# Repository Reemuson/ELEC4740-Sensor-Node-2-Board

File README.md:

<h1 align="center">SN2 BREAKOUT BOARD</h1>

<p align="center" width="100%">
  
</p>

***

<p align="center">
  
&nbsp; &nbsp; &nbsp; &nbsp;
  
</p>

***

## SPECIFICATIONS

| Parameter | Value | 
| --- | --- |
| Dimensions | 100.0 × 100.0 mm |

***

## DIRECTORY STRUCTURE

    .
    ├─ Computations       # Misc calculations
    ├─ HTML               # HTML files for generated webpage
    ├─ Images             # Pictures and renders
    │
    ├─ kibot_resources    # External resources for KiBot
    │  ├─ colors          # Color theme for KiCad
    │  ├─ fonts           # Fonts used in the project
    │  ├─ scripts         # External scripts used with KiBot
    │  └─ templates       # Templates for KiBot generated reports
    │
    ├─ kibot_yaml         # KiBot YAML config files
    ├─ KiRI               # KiRI (PCB diff viewer) files
    │
    ├─ lib                # KiCad footprint and symbol libraries
    │  ├─ 3d_models       # Component 3D models
    │  ├─ lib_fp          # Footprint libraries
    │  └─ lib_sym         # Symbol libraries
    │
    ├─ Logos              # Logos
    │
    ├─ Manufacturing      # Assembly and fabrication documents
    │  ├─ Assembly        # Assembly documents (BoM, pos, notes)
    │  │
    │  └─ Fabrication     # Fabrication documents (ZIP, notes)
    │     ├─ Drill Tables # CSV drill tables
    │     └─ Gerbers      # Gerbers
    │
    ├─ Report             # Reports for ERC/DRC
    ├─ Schematic          # PDF of schematic
    ├─ Templates          # Title block templates
    ├─ Testing
    │  └─ Testpoints      # Testpoints tables      
    │
    └─ Variants           # Outputs for assembly variants

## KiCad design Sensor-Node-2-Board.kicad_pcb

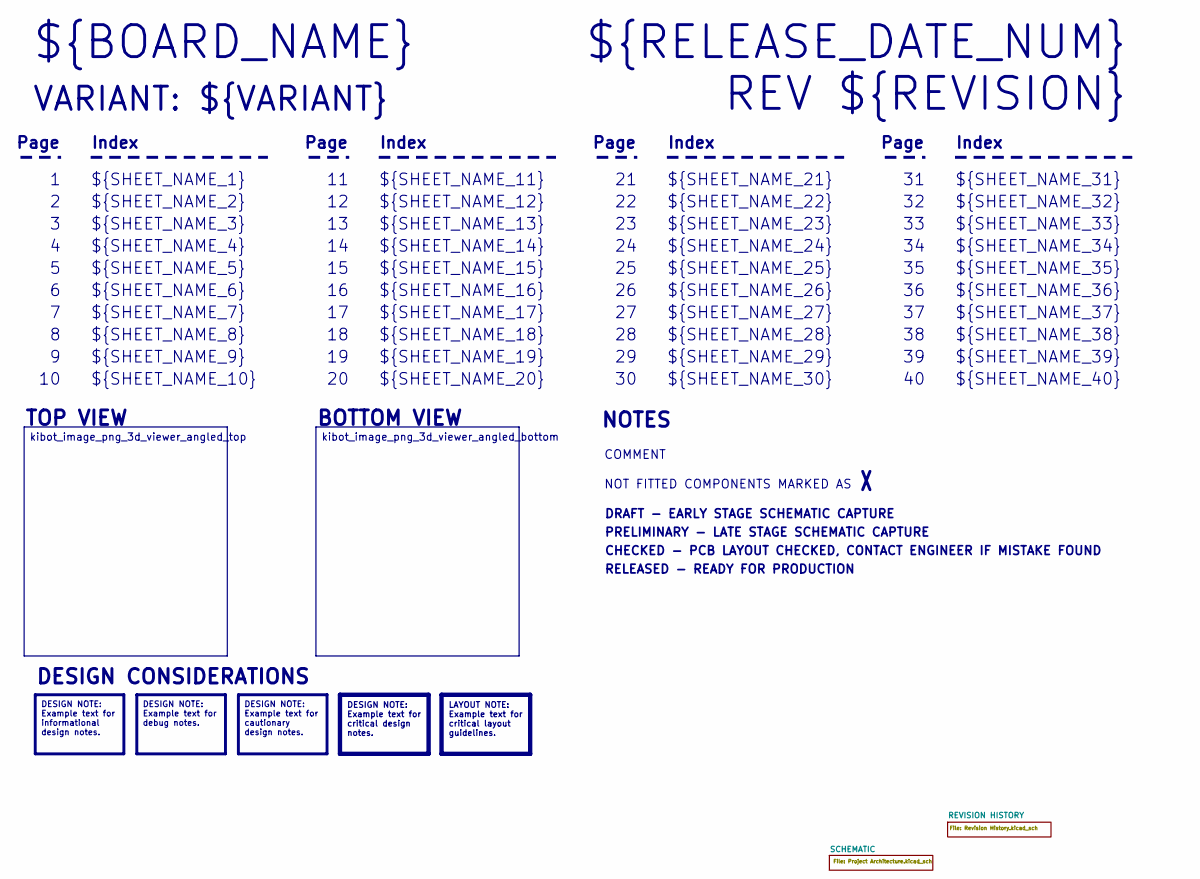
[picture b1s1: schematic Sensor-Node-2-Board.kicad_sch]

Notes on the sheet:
VARIANT: ${VARIANT}
RELEASED - READY FOR PRODUCTION
${SHEET_NAME_24}
Index
Page
PRELIMINARY - LATE STAGE SCHEMATIC CAPTURE
${SHEET_NAME_22}
DRAFT - EARLY STAGE SCHEMATIC CAPTURE
${SHEET_NAME_12}
${SHEET_NAME_8}
${SHEET_NAME_2}
${SHEET_NAME_5}
${SHEET_NAME_20}
${SHEET_NAME_23}
${RELEASE_DATE_NUM}
${SHEET_NAME_35}
NOT FITTED COMPONENTS MARKED AS
${SHEET_NAME_11}
${SHEET_NAME_6}
${SHEET_NAME_37}
${SHEET_NAME_26}
${SHEET_NAME_36}
REV ${REVISION}
${SHEET_NAME_15}
CHECKED - PCB LAYOUT CHECKED, CONTACT ENGINEER IF MISTAKE FOUND
BOTTOM VIEW
${SHEET_NAME_14}
${SHEET_NAME_21}
${SHEET_NAME_17}
${SHEET_NAME_18}
${SHEET_NAME_7}
${SHEET_NAME_31}
${BOARD_NAME}
NOTES
${SHEET_NAME_40}
${SHEET_NAME_39}
${SHEET_NAME_32}
${SHEET_NAME_1}
${SHEET_NAME_9}
${SHEET_NAME_38}

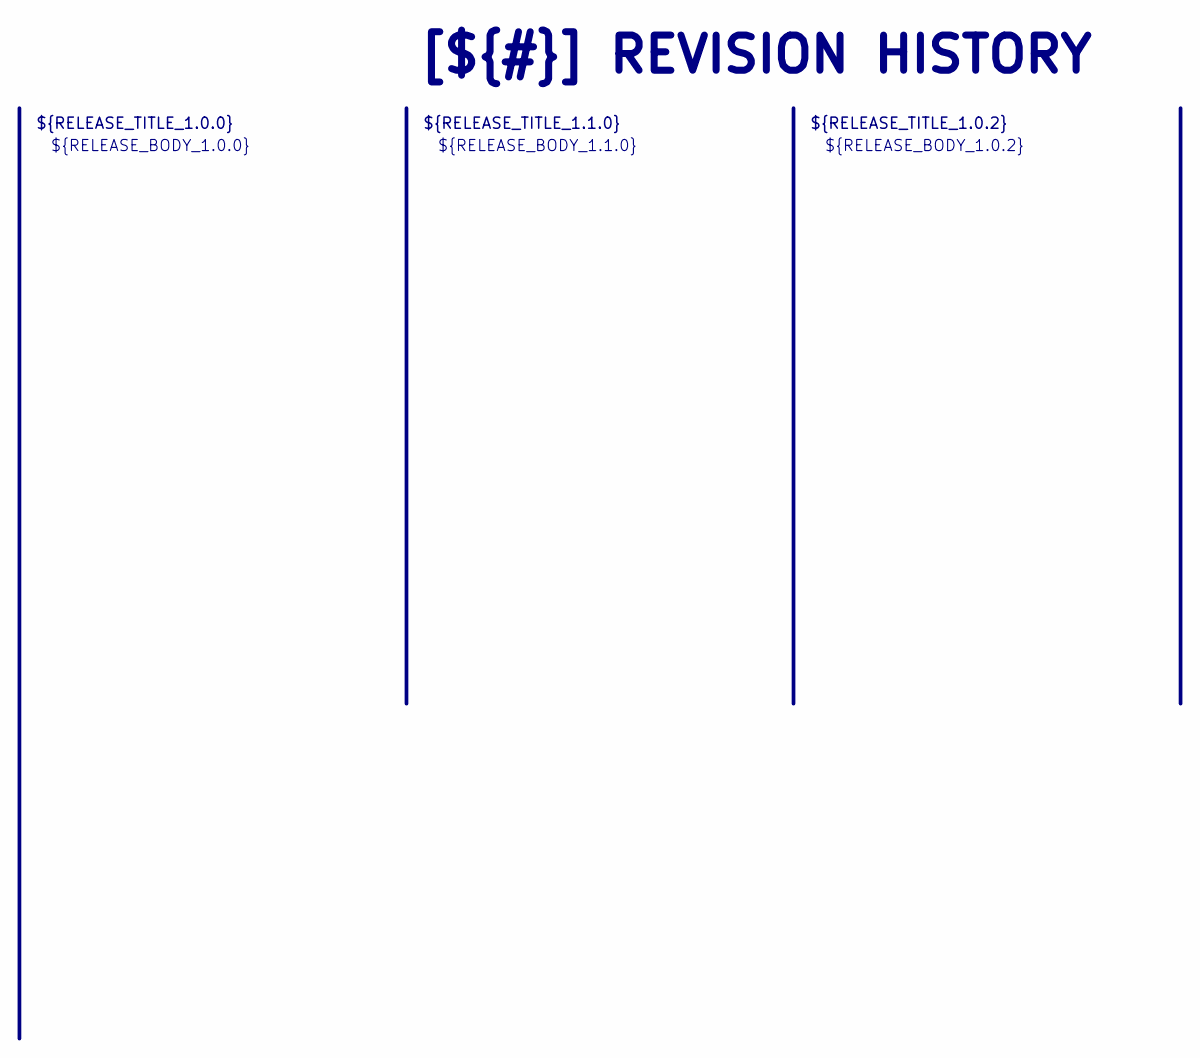
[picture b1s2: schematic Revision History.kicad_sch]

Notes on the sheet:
[${#}] ${TITLE}
${RELEASE_BODY_1.0.0}
${RELEASE_TITLE_1.0.2}
${RELEASE_BODY_1.0.2}
${RELEASE_BODY_1.1.0}
${RELEASE_TITLE_1.0.0}
${RELEASE_TITLE_1.1.0}

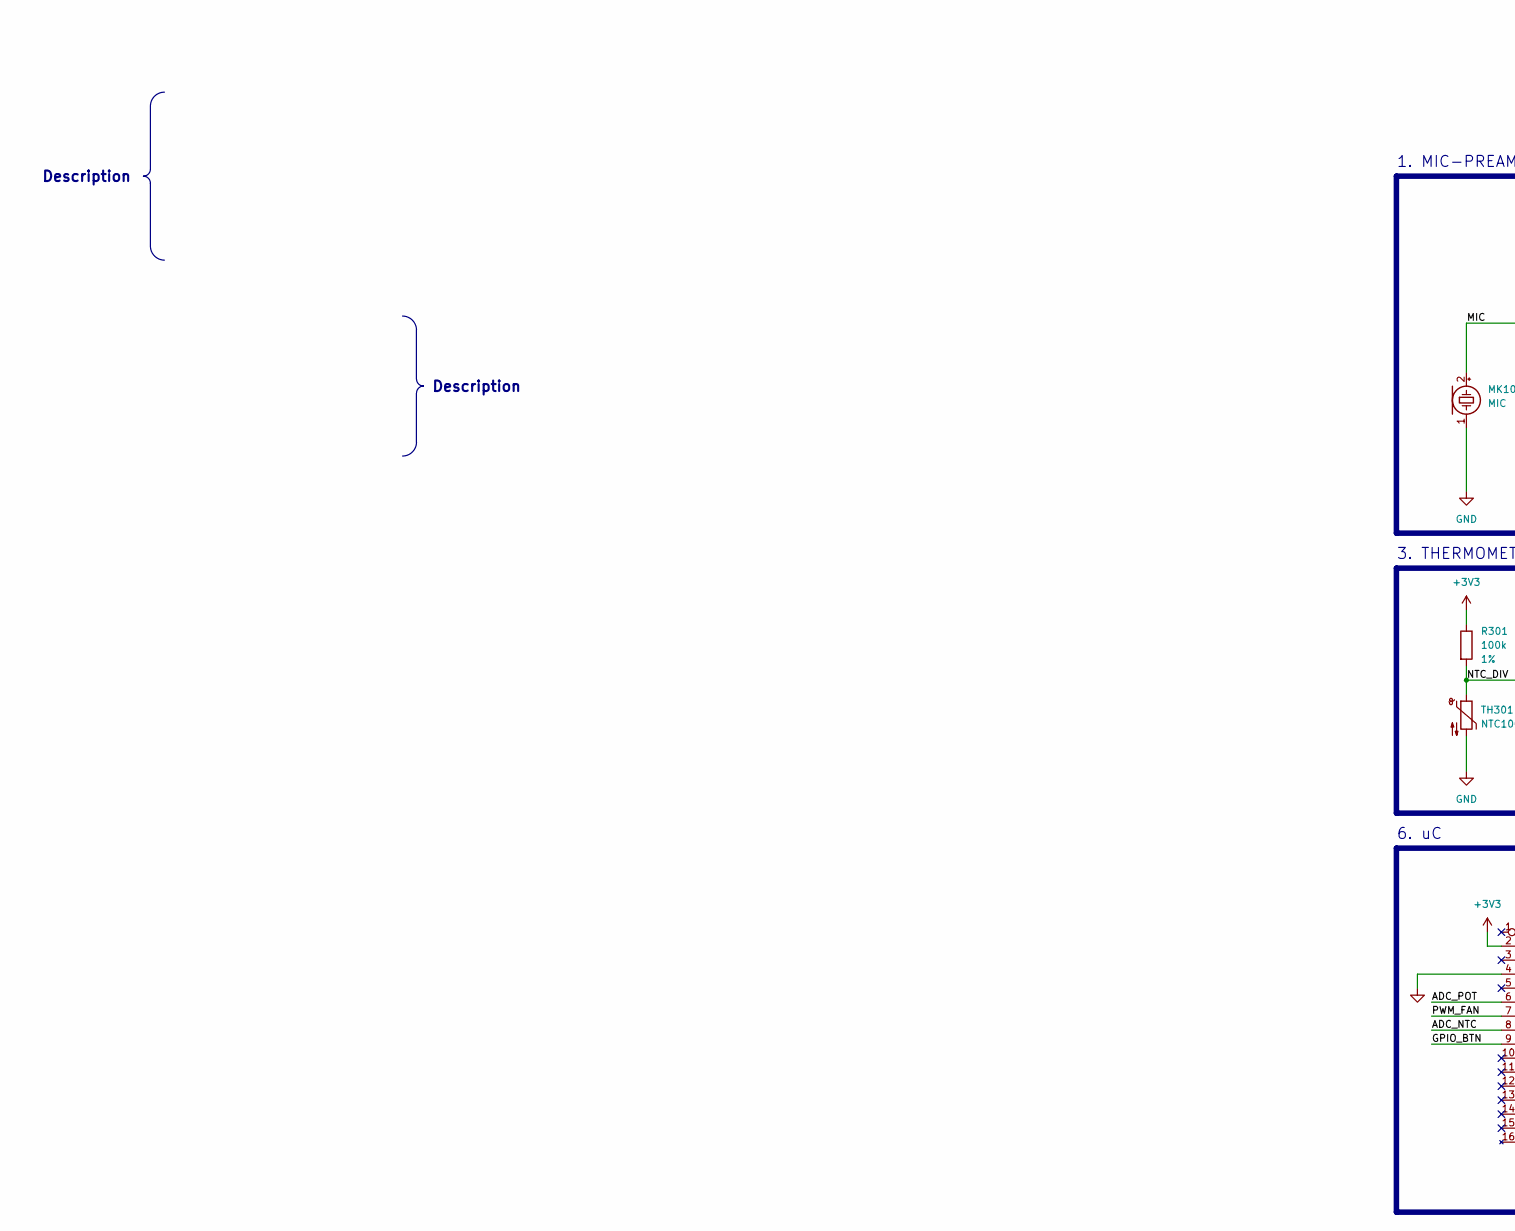
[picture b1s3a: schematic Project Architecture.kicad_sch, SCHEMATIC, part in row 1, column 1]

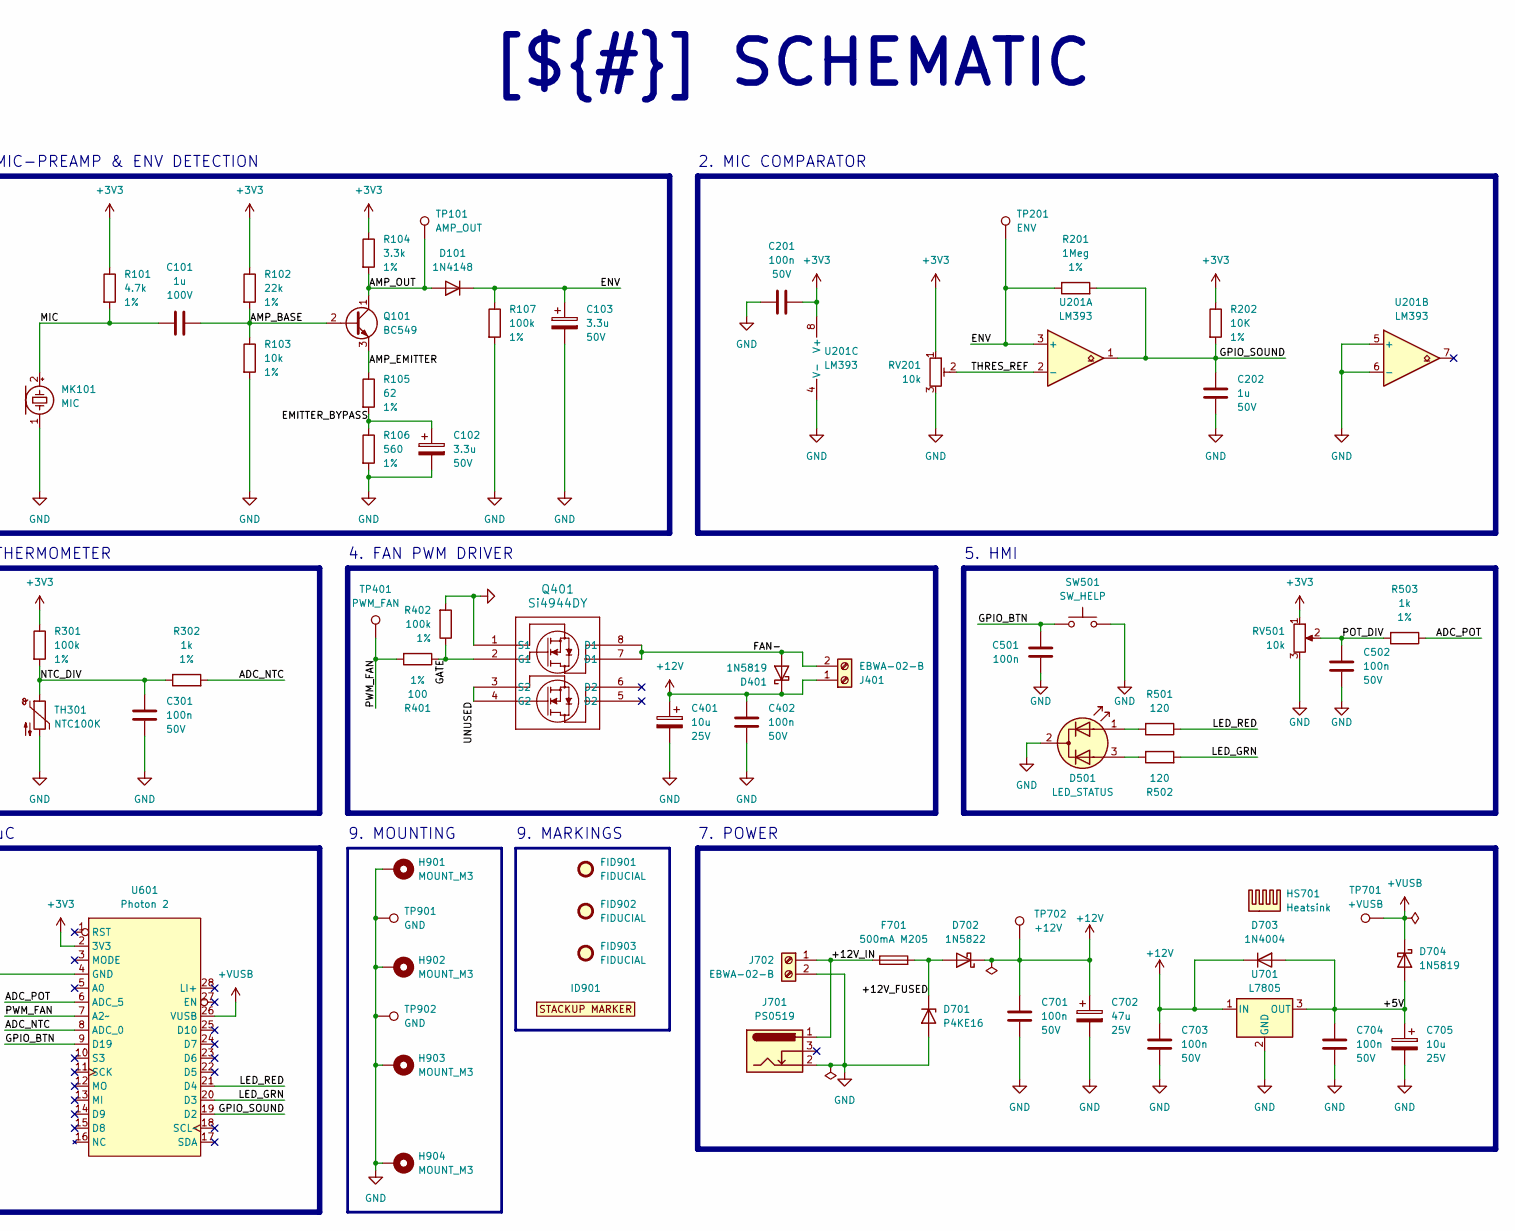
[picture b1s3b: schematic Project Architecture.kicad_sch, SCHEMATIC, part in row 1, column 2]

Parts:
C101: 1u; C_Rect_L16.5mm_W6.0mm_P15.00mm_MKT; Voltage 100V
C102, C103: 3.3u; CP_Radial_D5.0mm_P2.00mm; Voltage 50V; Tolerance 10%
C201, C301, C402, C501, C502, C701, C703, C704: 100n; C_Disc_D5.0mm_W2.5mm_P5.00mm; Tolerance 20%; Voltage 50V
C202: 1u; C_Disc_D5.0mm_W2.5mm_P5.00mm; Voltage 50V
C401, C705: 10u; CP_Radial_D5.0mm_P2.00mm; Voltage 25V
C702: 47u; CP_Radial_D8.0mm_P3.50mm; Voltage 25V
D101: 1N4148; D_DO-35_SOD27_P5.08mm_Vertical_AnodeUp
D401: 1N5819; D_DO-41_SOD81_P7.62mm_Horizontal
D501: LED_STATUS; LED_D5.0mm-3
D701: P4KE16; D_DO-41_SOD81_P10.16mm_Horizontal
D702: 1N5822; D_DO-201AD_P15.24mm_Horizontal
D703: 1N4004; D_DO-41_SOD81_P7.62mm_Horizontal
D704: 1N5819; D_DO-41_SOD81_P12.70mm_Horizontal
F701: 500mA M205; Fuseholder_Clip-5x20mm_Eaton_1A5601-01_Inline_P20.80x6.76mm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
FID901, FID902, FID903: FIDUCIAL; Fiducial_1mm_Mask2mm
H901, H902, H903, H904: MOUNT_M3; MountingHole_3.2mm_M3_ISO7380_Pad
HS701: Heatsink; Heatsink_6073B_19x9.5mm
ID901: BOARD_STACKUP_MARKER; STACKUP_ID_2L
J401, J702: EBWA-02-B; TerminalBlock_Phoenix_MKDS-1,5-2_1x02_P5.00mm_Horizontal
J701: PS0519; BarrelJack_Kycon_KLDX-0202-xC_Horizontal
MK101: MIC; POM-2244P-C3310-2-R
Q101: BC549; TO-92_Inline
Q401: Si4944DY; SO-8_3.9x4.9mm_P1.27mm
R101: 4.7k; R_Axial_DIN0309_L9.0mm_D3.2mm_P12.70mm_Horizontal; Tolerance 1%
R102: 22k; R_Axial_DIN0309_L9.0mm_D3.2mm_P12.70mm_Horizontal; Tolerance 1%
R103: 10k; R_Axial_DIN0309_L9.0mm_D3.2mm_P12.70mm_Horizontal; Tolerance 1%
R104: 3.3k; R_Axial_DIN0309_L9.0mm_D3.2mm_P12.70mm_Horizontal; Tolerance 1%
R105: 62; R_Axial_DIN0309_L9.0mm_D3.2mm_P12.70mm_Horizontal; Tolerance 1%
R106: 560; R_Axial_DIN0309_L9.0mm_D3.2mm_P12.70mm_Horizontal; Tolerance 1%
R107, R301, R402: 100k; R_Axial_DIN0309_L9.0mm_D3.2mm_P12.70mm_Horizontal; Tolerance 1%
R201: 1Meg; R_Axial_DIN0309_L9.0mm_D3.2mm_P5.08mm_Vertical; Tolerance 1%
R202: 10K; R_Axial_DIN0309_L9.0mm_D3.2mm_P12.70mm_Horizontal; Tolerance 1%
R302, R503: 1k; R_Axial_DIN0309_L9.0mm_D3.2mm_P12.70mm_Horizontal; Tolerance 1%
R401: 100; R_Axial_DIN0309_L9.0mm_D3.2mm_P12.70mm_Horizontal; Tolerance 1%
R501, R502: 120; R_Axial_DIN0309_L9.0mm_D3.2mm_P12.70mm_Horizontal; Tolerance 1%
RV201: 10k; Potentiometer_Bourns_3296W_Vertical
RV501: 10k; Potentiometer_Omeg_PC16BU_Vertical
SW501: SW_HELP; SW_SPST_Omron_B3F-40xx
TH301: NTC100K; PinHeader_1x02_P2.54mm_Vertical
TP101: AMP_OUT; TestPoint_Loop_D1.80mm_Drill1.0mm_Beaded
TP201: ENV; TestPoint_Loop_D1.80mm_Drill1.0mm_Beaded
TP401: PWM_FAN; TestPoint_Loop_D1.80mm_Drill1.0mm_Beaded
TP701: +VUSB; TestPoint_Loop_D1.80mm_Drill1.0mm_Beaded
TP702: +12V; TestPoint_Loop_D1.80mm_Drill1.0mm_Beaded
TP901, TP902: GND; TestPoint_Loop_D1.80mm_Drill1.0mm_Beaded
U201: LM393; DIP-8_W7.62mm_Socket
U601: Photon 2; PHOTON2
U701: L7805; TO-220-3_Vertical

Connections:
+3V3: C201.1, R101.1, R102.1, R104.1, R202.1, R301.1, RV201.1, RV501.1, U201.8 (V+), U601.2 (3V3)
+12V: C401.1, C402.1, C701.2, C702.1, C703.2, D401.1 (K), D702.1 (K), D703.1 (K), J401.1, TP702.1, U701.1 (IN)
+VUSB: D704.1 (K), TP701.1, U601.26 (VUSB)
/SCHEMATIC/+5V: C704.2, C705.1, D703.2 (A), D704.2 (A), U701.3 (OUT)
/SCHEMATIC/+12V_FUSED: D701.1 (K), D702.2 (A), F701.2
/SCHEMATIC/+12V_IN: F701.1, J701.1, J702.1
/SCHEMATIC/ADC_NTC: R302.2, U601.8 (ADC_0)
/SCHEMATIC/ADC_POT: R503.1, U601.6 (ADC_5)
/SCHEMATIC/AMP_BASE: C101.2, Q101.2 (B), R102.2, R103.1
/SCHEMATIC/AMP_EMITTER: Q101.3 (E), R105.1
/SCHEMATIC/AMP_OUT: D101.2 (A), Q101.1 (C), R104.2, TP101.1
/SCHEMATIC/EMITTER_BYPASS: C102.1, R105.2, R106.1
/SCHEMATIC/ENV: C103.1, D101.1 (K), R107.1, R201.1, TP201.1, U201.3 (+)
/SCHEMATIC/FAN-: D401.2 (A), J401.2, Q401.7 (D1), Q401.8 (D1)
/SCHEMATIC/GATE: Q401.2 (G1), R401.1, R402.1
/SCHEMATIC/GPIO_BTN: C501.1, SW501.1, U601.9 (D19)
/SCHEMATIC/GPIO_SOUND: C202.1, R201.2, R202.2, U201.1, U601.19 (D2)
/SCHEMATIC/LED_GRN: R502.2, U601.20 (D3)
/SCHEMATIC/LED_RED: R501.1, U601.21 (D4)
/SCHEMATIC/MIC: C101.1, MK101.2 (+), R101.2
/SCHEMATIC/NTC_DIV: C301.1, R301.2, R302.1, TH301.1
/SCHEMATIC/POT_DIV: C502.2, R503.2, RV501.2
/SCHEMATIC/PWM_FAN: R401.2, TP401.1, U601.7 (A2~)
/SCHEMATIC/THRES_REF: RV201.2, U201.2 (-)
/SCHEMATIC/UNUSED: Q401.3 (S2), Q401.4 (G2)
GND: C102.2, C103.2, C201.2, C202.2, C301.2, C401.2, C402.2, C501.2, C502.1, C701.1, C702.2, C703.1, C704.1, C705.2, D501.2 (K), D701.2 (A), H901.1, H902.1, H903.1, H904.1, J701.2, J702.2, MK101.1 (-), Q401.1 (S1), R103.2, R106.2, R107.2, R402.2, RV201.3, RV501.3, SW501.2, TH301.2, TP901.1, TP902.1, U201.4 (V-), U201.5 (+), U201.6 (-), U601.4 (GND), U701.2 (GND)
unnamed: D501.1 (A1), R501.2
unnamed: D501.3 (A2), R502.1

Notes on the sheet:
6. uC
9. MARKINGS
2. MIC COMPARATOR
9. MOUNTING
3. THERMOMETER
7. POWER
5. HMI
4. FAN PWM DRIVER
1. MIC-PREAMP & ENV DETECTION
Description
[${#}] ${TITLE}

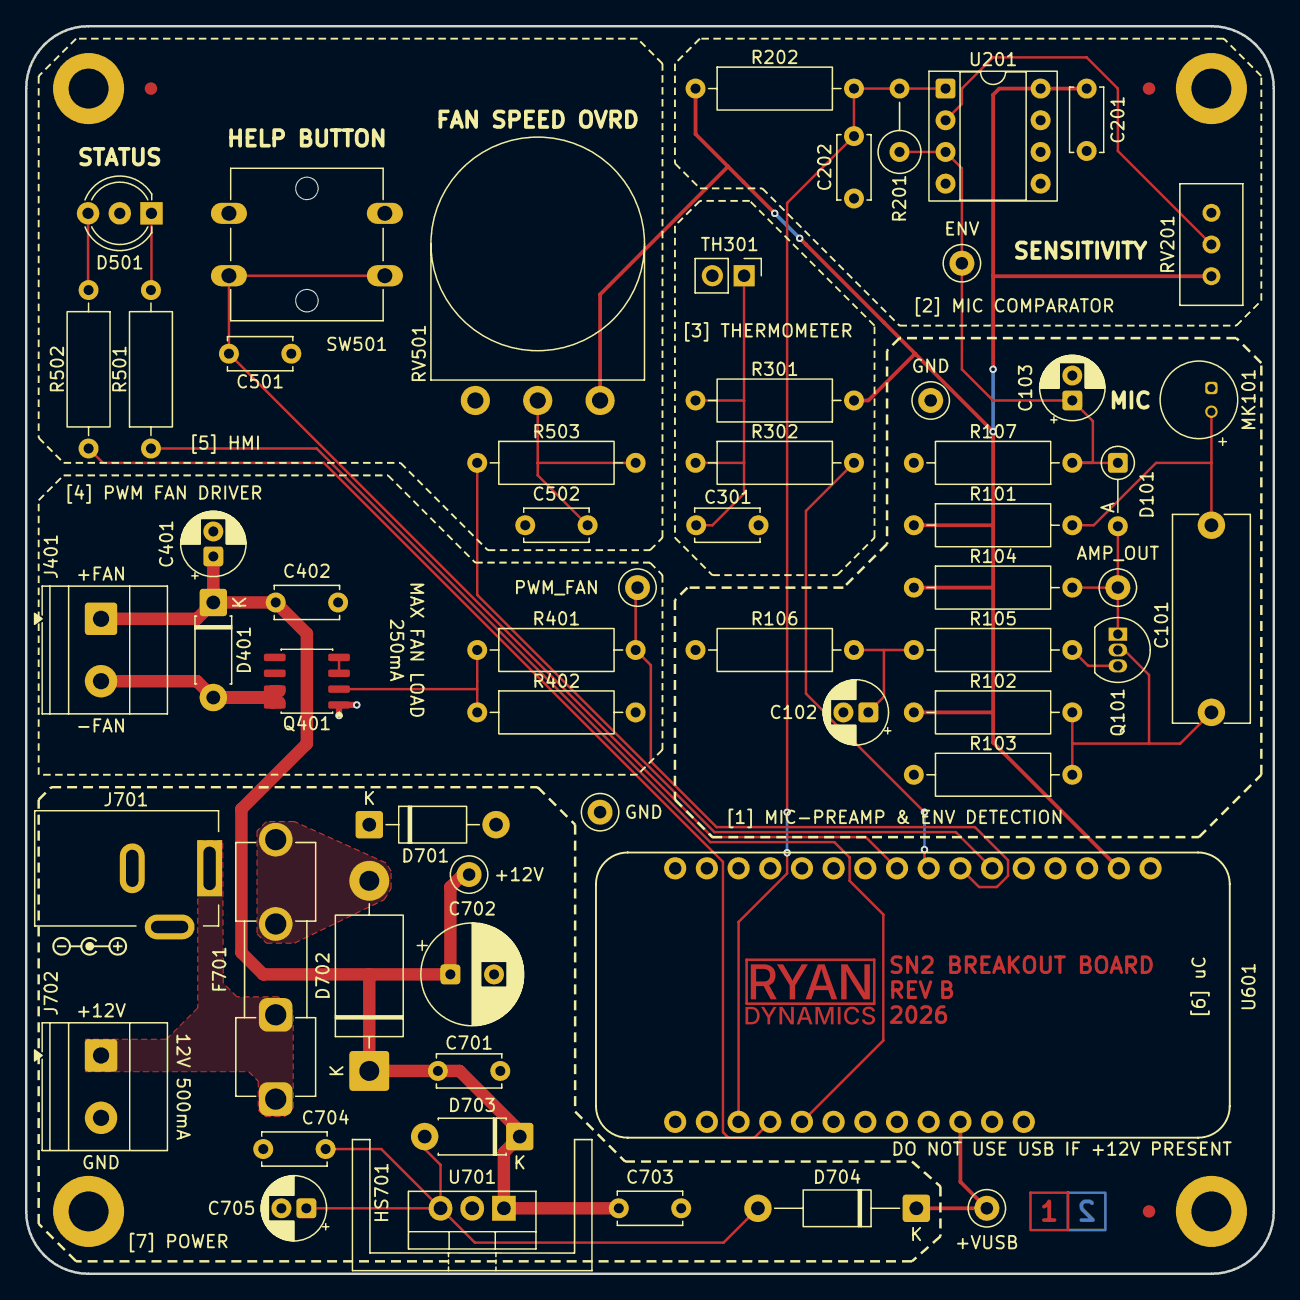
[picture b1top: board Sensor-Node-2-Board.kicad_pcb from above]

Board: 2 copper layers, 100.0 x 100.0 mm, 68 parts (0 on the bottom side), 28 nets.

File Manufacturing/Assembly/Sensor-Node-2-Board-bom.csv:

Row,Quantity Per PCB,References,Value,Datasheet,Footprint,Description,Tolerance,Voltage,Manufacturer,MPN,Supplier,SPN,Notes
1,8,C201 C301 C402 C501 C502 C701 C703 C704,100n,~,C_Disc_D5.0mm_W2.5mm_P5.00mm,CAP CER Y5U 100N 50V 20% P=5MM,20%,50V,,,Jaycar Electronics,RC5360,
2,2,C101 C202,1u,~,C_Rect_L16.5mm_W6.0mm_P15.00mm_MKT,CAP GRN 1U 100V P=11MM CAP MONO 1U 50V,,100V 50V,,,Jaycar Electronics,RG5170,
3,2,C102 C103,3.3u,~,CP_Radial_D5.0mm_P2.00mm,CAP LL CD81 RB 3U3 50V P=2MM 5X11MM,10%,50V,,,Jaycar Electronics,RL6422,
4,2,C401 C705,10u,~,CP_Radial_D5.0mm_P2.00mm,Polarized capacitor,,25V,,,,,
5,1,C702,47u,~,CP_Radial_D8.0mm_P3.50mm,Polarized capacitor,,25V,,,,,
6,1,D703,1N4004,http://www.vishay.com/docs/88503/1n4001.pdf,D_DO-41_SOD81_P7.62mm_Horizontal,"400V 1A General Purpose Rectifier Diode, DO-41",,,,,,,
7,1,D101,1N4148,https://assets.nexperia.com/documents/data-sheet/1N4148_1N4448.pdf,D_DO-35_SOD27_P5.08mm_Vertical_AnodeUp,DIODE 1N4148 FAST 100V 250MA DO41,,,,,Jaycar Electronics,,
8,2,D401 D704,1N5819,http://www.vishay.com/docs/88525/1n5817.pdf,D_DO-41_SOD81_P7.62mm_Horizontal,DIODE 1N5819 SCHOTTKY 40V 1A DO41,,,,,Jaycar Electronics,ZR1020,
9,1,D702,1N5822,http://www.vishay.com/docs/88526/1n5820.pdf,D_DO-201AD_P15.24mm_Horizontal,DIODE 1N5822 SCHOTTKY 40V 3A DO41,,,,,Jaycar Electronics,ZR1023,
10,1,D501,LED_STATUS,~,LED_D5.0mm-3,LED 5MM DIF BICOL COM CATH ORG/GRN 70/80,,,,,Jaycar Electronics,ZD0252,
11,1,D701,P4KE16,~,D_DO-41_SOD81_P10.16mm_Horizontal,DIODE TVS UNIDIRECTIONAL,,,,,,,
12,1,F701,500mA M205,~,Fuseholder_Clip-5x20mm_Eaton_1A5601-01_Inline_P20.80x6.76mm_D1.70mm_Horizontal,Fuse,,,,,,,
13,1,HS701,Heatsink,~,Heatsink_6073B_19x9.5mm,Heatsink,,,,,,,
14,3,J401 J701 J702,EBWA-02-B,~,"TerminalBlock_Phoenix_MKDS-1,5-2_1x02_P5.00mm_Horizontal",TERMINAL PCB SCREW 2WAY BLU P=5MM SKT PCB DC SPST SWITCHED 2.1MM,,,,,Jaycar Electronics,HM3412,
15,1,MK101,MIC,~,POM-2244P-C3310-2-R,MIC PCB 2PIN 1.5V D10XH6.5MM,,,,,Jaycar Electronics,AM4011,
16,1,Q101,BC549,https://www.onsemi.com/pub/Collateral/BC550-D.pdf,TO-92_Inline,TRAN BC540 NPN 30V 100MA TO92,,,,,,,
17,1,Q401,Si4944DY,https://www.digikey.com.au/en/htmldatasheets/production/8313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,SO-8_3.9x4.9mm_P1.27mm,SMD MOSFET SI4944DY DUAL N-CH 30V SOIC8,,,,,Jaycar Electronics,ZK8821,
18,1,R105,62,~,R_Axial_DIN0309_L9.0mm_D3.2mm_P12.70mm_Horizontal,RES 0.5W CARB 62R,1%,,,,,,
19,1,R401,100,~,R_Axial_DIN0309_L9.0mm_D3.2mm_P12.70mm_Horizontal,RES 0.5W CARB 100R,1%,,,,,,
20,2,R501 R502,120,~,R_Axial_DIN0309_L9.0mm_D3.2mm_P12.70mm_Horizontal,RES 0.5W CARB 120R,1%,,,,,,
21,1,R106,560,~,R_Axial_DIN0309_L9.0mm_D3.2mm_P12.70mm_Horizontal,RES 0.5W CARB 560R,1%,,,,,,
22,2,R302 R503,1k,~,R_Axial_DIN0309_L9.0mm_D3.2mm_P12.70mm_Horizontal,RES 0.5W CARB 1K,1%,,,,,,
23,1,R104,3.3k,~,R_Axial_DIN0309_L9.0mm_D3.2mm_P12.70mm_Horizontal,RES 0.5W CARB 3.3K,1%,,,,,,
24,1,R101,4.7k,~,R_Axial_DIN0309_L9.0mm_D3.2mm_P12.70mm_Horizontal,RES 0.5W CARB 4.7K,1%,,,,,,
25,4,R103 R202 RV201 RV501,10k,~,R_Axial_DIN0309_L9.0mm_D3.2mm_P12.70mm_Horizontal,RES 0.5W CARB 10K TRIMPOT 25TURN 10K TOP ADJ POT PCB LIN SG 16MM B10K STD IMP SHAFT,1%,,,,Jaycar Electronics,RT4650 RP7510,
26,1,R102,22k,~,R_Axial_DIN0309_L9.0mm_D3.2mm_P12.70mm_Horizontal,RES 0.5W CARB 22K,1%,,,,,,
27,3,R107 R301 R402,100k,~,R_Axial_DIN0309_L9.0mm_D3.2mm_P12.70mm_Horizontal,RES 0.5W CARB 100K,1%,,,,,,
28,1,R201,1Meg,~,R_Axial_DIN0309_L9.0mm_D3.2mm_P5.08mm_Vertical,RES 0.5W CARB 1M,1%,,,,,,
29,1,SW501,SW_HELP,~,SW_SPST_Omron_B3F-40xx,SWITCH PCB TACT SPST SQR STEM 11.9X11.9,,,,,Jaycar Electronics,SP0608,
30,1,TH301,NTC100K,~,PinHeader_1x02_P2.54mm_Vertical,THERMISTOR NTC GLASS 100KR 250DEG,,,,,Jaycar Electronics,RN3446,
31,1,U701,L7805,http://www.st.com/content/ccc/resource/technical/document/da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,TO-220-3_Vertical,VREG 7805 +5V 1A TO220,,,,,Jaycar Electronics,ZV1505,
32,1,U201,LM393,http://www.ti.com/lit/ds/symlink/lm393.pdf,DIP-8_W7.62mm_Socket,IC LM393N LO-PWR DUAL COMPARATOR DIP8,,,,,Jaycar Electronics,ZL3393,
33,1,U601,Photon 2,https://docs.particle.io/reference/datasheets/wi-fi/photon-2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,PHOTON2,PHOTON 2 [X1],,,,,,,

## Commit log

2026-02-19 feat: initial commit
2026-02-19 Update Outputs
2026-02-19 fix: pcb dimensioning
2026-02-19 fix: pcb fab/assembly doc layout
2026-02-19 fix: force pcb outs to A3
2026-02-19 feat: release
2026-02-19 fix: image in readme
2026-02-19 Update CHANGELOG
2026-02-19 Update Outputs (release)
2026-02-28 fix: change status led wiring and improve 12V input protection
2026-02-28 fix: rename board_REV-A.jpg to board-REV-A.jpg
